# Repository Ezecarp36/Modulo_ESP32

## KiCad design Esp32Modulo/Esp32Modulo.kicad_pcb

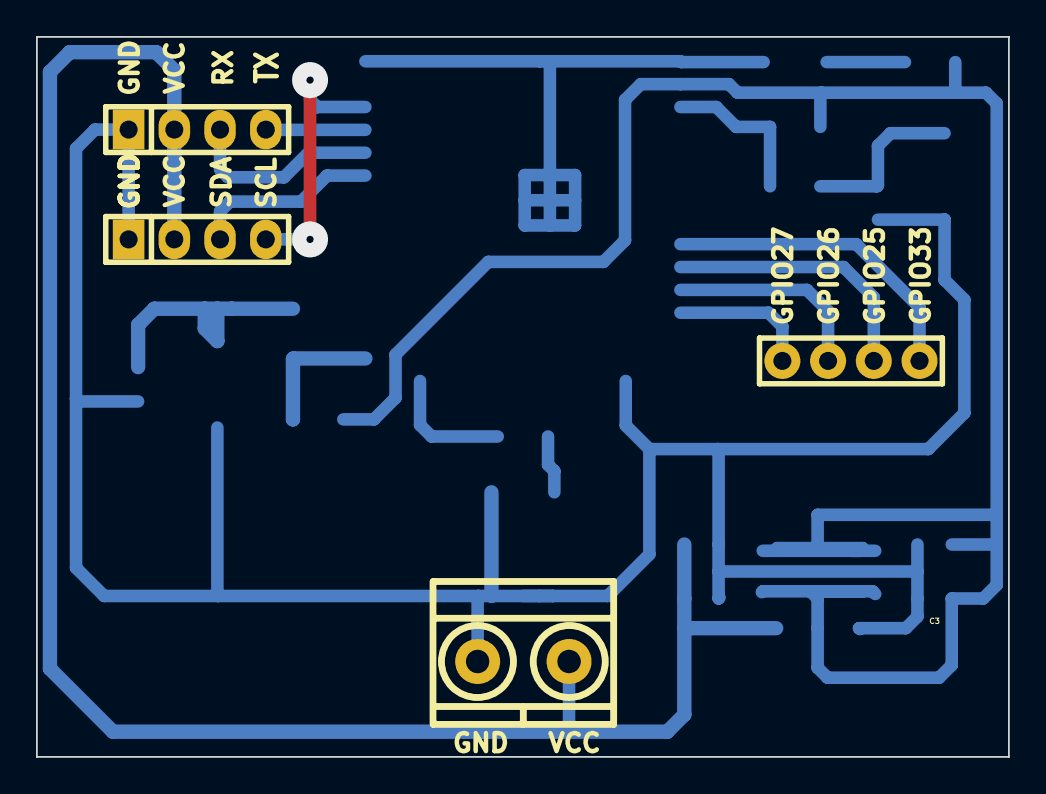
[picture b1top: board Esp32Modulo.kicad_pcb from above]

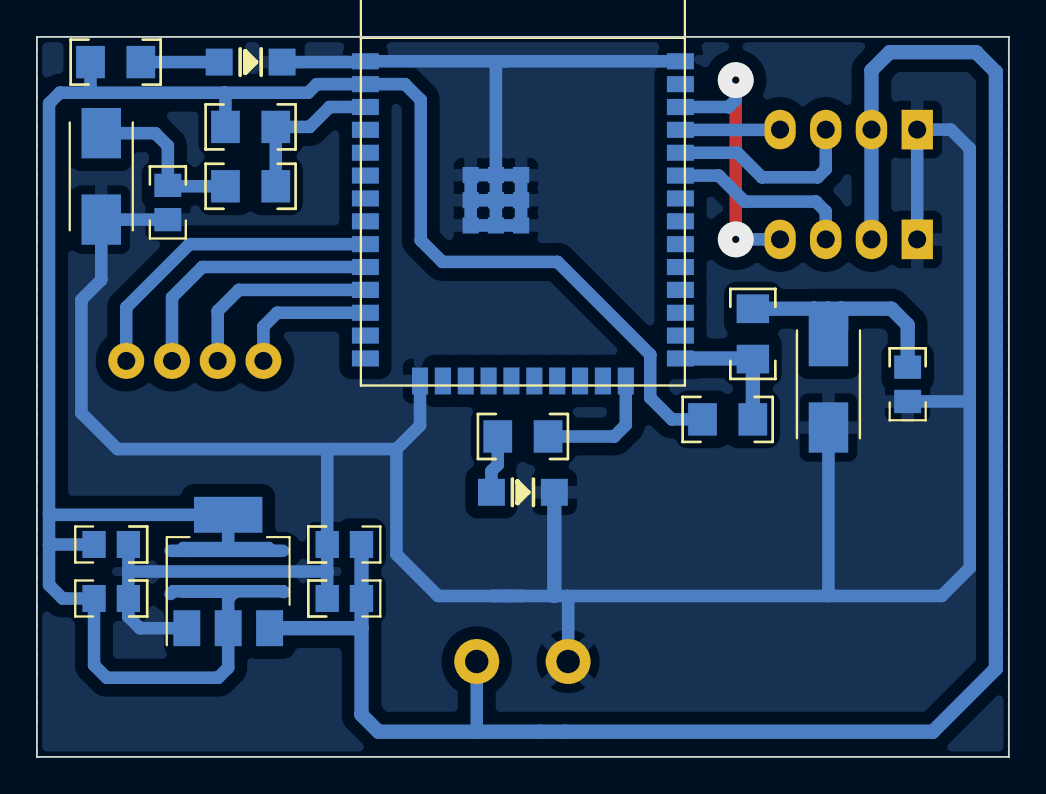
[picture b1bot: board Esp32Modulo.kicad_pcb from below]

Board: 2 copper layers, 54.0 x 40.0 mm, 22 parts (18 on the bottom side), 18 nets.

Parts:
BOOT1: SW_Push; Button
C1, C3: 10uF; C_0805
C2, C4: 100nF; C_0805
C5, C6: 1n; C_0805
EN1: SW_Push; Button
J1: Programador; pin_strip_4
J2: Salidas_I2C(5V); pin_strip_4
J3: Salidas_GPIO; pin_strip_4
J4: Alimentacion; BORNERA2_AZUL
LED1: POW; LED_1206
LED2: D2; LED_1206
R1, R7: 470; R_1206
R3: 1OK; R_1206
R5, R6: 1K; R_1206
R8: 10K; R_1206
U1: ESP32-WROOM-32E
U2: AMS1117-3.3; SOT-223-3_TabPin2

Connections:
+3V3: C3.1, C4.1, R3.2, R5.2, R8.2, U1.3V3, U2.2 (VO)
+5V: C1.1, C2.1, J1.2, J2.2, J4.2, U2.3 (VI)
/EN: R7.2, R8.1, U1.9 (EN)
/IO0: R1.2, R3.1, U1.23 (IO0)
/IO2: R6.2, U1.22 (IO2)
/IO25: J3.3, U1.14 (IO25)
/IO26: J3.2, U1.15 (IO26)
/IO27: J3.1, U1.16 (IO27)
/IO33: J3.4, U1.13 (IO33)
/RXD0: J1.3, U1.40 (RXD0)
/SCL: J2.4, U1.39 (IO22)
/SDA: J2.3, U1.42 (IO21)
/TXD0: J1.4, U1.41 (TXD0)
GND: BOOT1.1, C1.2, C2.2, C3.2, C4.2, C5.1, C6.1, EN1.1, J1.1, J2.1, J4.1, LED1.2 (K), LED2.2 (K), U1.GND, U2.1 (GND)
unnamed: BOOT1.2, C5.2, R1.1
unnamed: C6.2, EN1.2, R7.1
unnamed: LED1.1 (A), R5.1
unnamed: LED2.1 (A), R6.1

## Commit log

2023-06-11 modificaciones al PCB para arreglar el error de pasar pistas por encima de la antena
2023-06-11 PCB con el error de la antena corregido y terminado
2023-06-13 El esp32 funciono y subi unos codigos de prueba que funcionaron correctamente
